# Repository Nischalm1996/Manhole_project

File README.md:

# Manhole_project

## Pin Connection from Board 
| Pin Name  | Digital Pin                            |
|-----------|----------------------------------------|
|SCK        | D13                                    |
| MOSI      | D11                                    |
| OK        | D6                                     |
| LEFT      | D10                                    |
| RIGHT     | D8                                     |
| RST       | D12                                    |
| RED       | D0                                     |
| GREEN     | A6                                     |
| BLUE      | A7                                     |
| MQ2       | A2                                     |
| MQ7       | A3                                     |
| MQ06      | A1                                     |
| MQ135     | A0                                     |

### MODULES USED
- DISPLAY 16x2 I2C
- SMOKE SENSOR (MQ02,MQ06,MQ07,MQ135)
- MQ02 (Methane, Butane, LPG, Hydrogen)
- MQ07 (CO, benzene)
- MQ06 (iso-butane, propane, LPG, LNG)
- MQ135 (NH3, NOx, alcohol,CO2)
- NAVIGATION BUTTON
- RGB LED
- GSM

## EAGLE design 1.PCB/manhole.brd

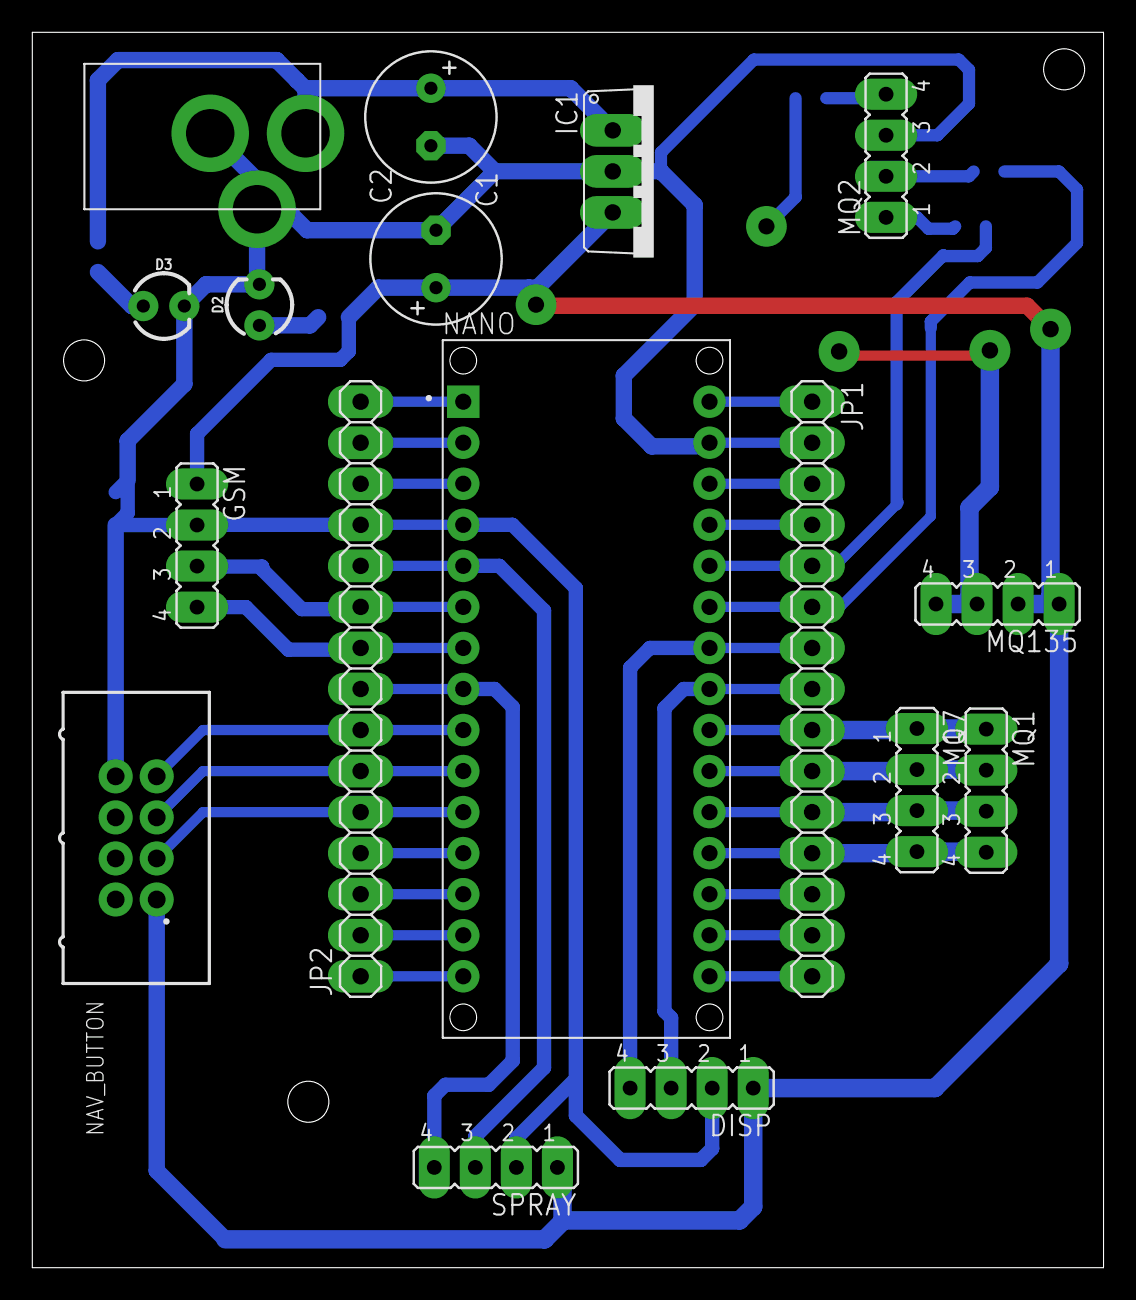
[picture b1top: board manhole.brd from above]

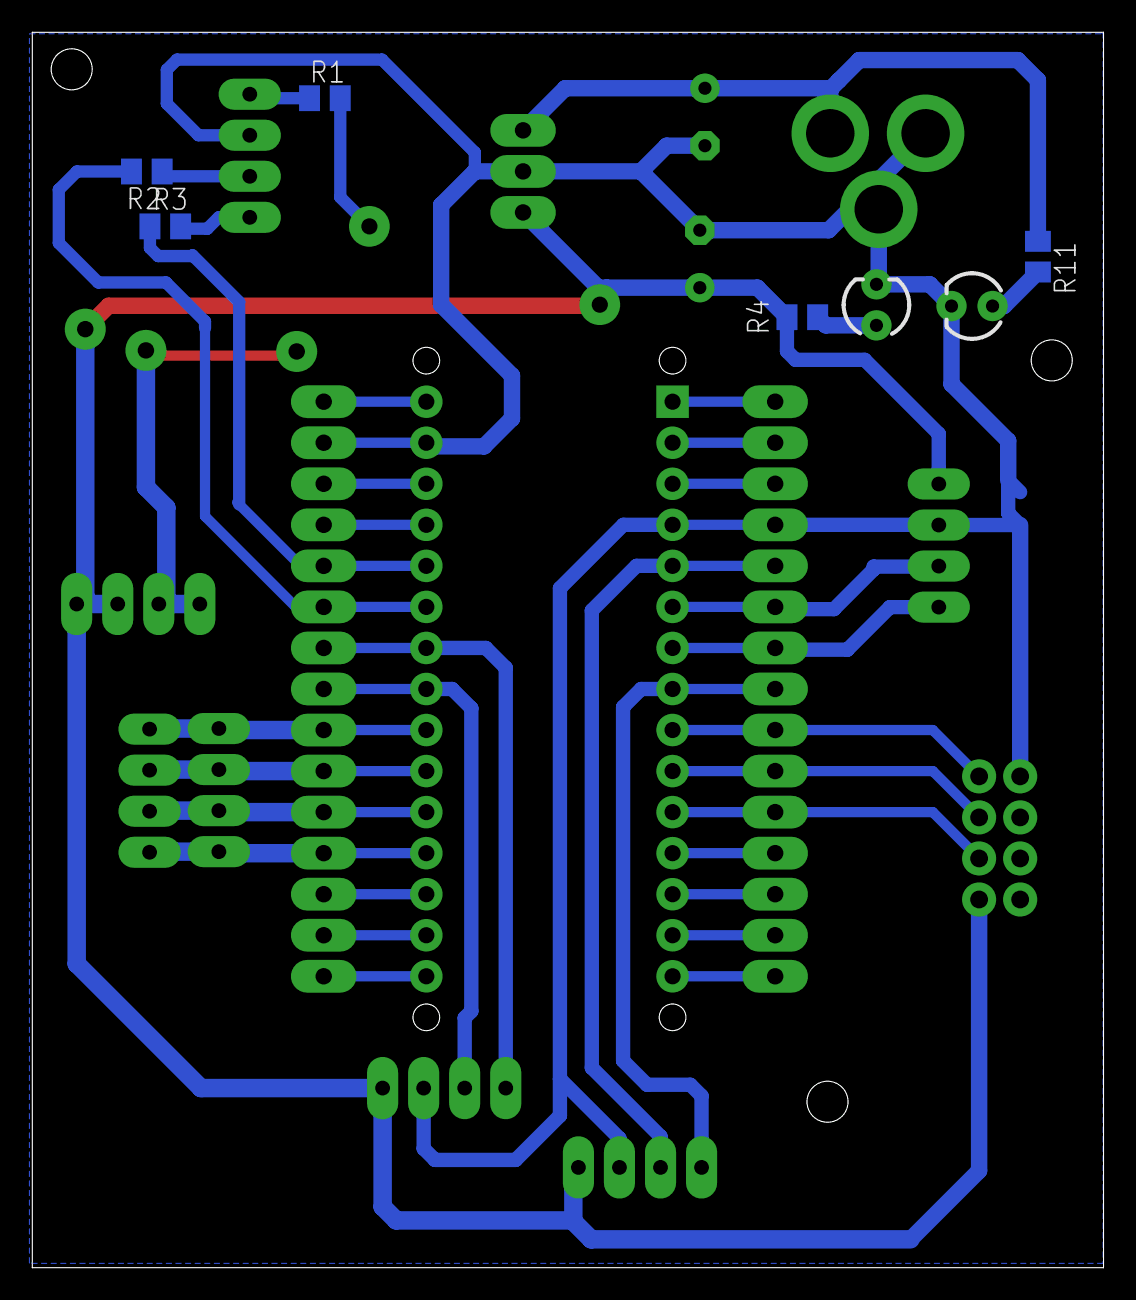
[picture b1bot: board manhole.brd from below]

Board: 2 copper layers, 66.3 x 76.5 mm, 22 parts (5 on the bottom side), 36 nets.

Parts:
C1, C2: E3,5-8
D2, D3: LED_3MM
DC_JACK: 2.1MMJACKTHM; PJ-102A
DISP: JP4
GSM: JP4
IC1: 7805TV; TO220V
JP1, JP2: 1X15
MQ1, MQ2, MQ7, MQ135: JP4
NANO: A000005; MODULE_A000005
NAV_BUTTON: 61200821621
R1, R2, R3: 300r; M0805
R4, R11: 1k; M0805
SPRAY: JP4

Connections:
3V3: JP1.14, NANO.17
5V: C2.+, DISP.1, GSM.1, IC1.3, MQ135.1, MQ135.2, NAV_BUTTON.1, R4.1, SPRAY.1
5V0: JP1.4, NANO.27
9_IN: C1.+, DC_JACK.TIP, IC1.1, R11.1
AREF: JP1.13, NANO.18
BLUE: MQ2.1, R3.1
BLUE1: JP1.5, NANO.26, R3.2
D0: JP2.15, NANO.1
D1: JP2.14, NANO.2
D9: JP2.4, NANO.12
GND: C1.-, C2.-, D2.K, D3.K, DC_JACK.RING, DC_JACK.RING_SW, DISP.2, GSM.2, IC1.2, JP1.2, JP2.12, MQ2.3, MQ135.3, MQ135.4, NANO.4, NANO.29, NAV_BUTTON.8, SPRAY.2
GREEN: MQ2.2, R2.1
GREEN1: JP1.6, NANO.25, R2.2
IN1: JP2.11, NANO.5, SPRAY.3
IN2: JP2.8, NANO.8, SPRAY.4
LEFT: JP2.6, NANO.10, NAV_BUTTON.5
MOSI: JP2.2, NANO.14
MQ2A0: JP1.9, MQ1.1, MQ7.1, NANO.22
MQ6A0: JP1.10, MQ1.2, MQ7.2, NANO.21
MQ7A0: JP1.11, MQ1.3, MQ7.3, NANO.20
MQ135A0: JP1.12, MQ1.4, MQ7.4, NANO.19
unnamed: D2.A, R4.2
unnamed: D3.A, R11.2
OK: JP2.7, NANO.9, NAV_BUTTON.7
RED: MQ2.4, R1.1
RED1: JP2.3, NANO.13, R1.2
RESET_1: JP2.13, NANO.3
RESET_2: JP1.3, NANO.28
RIGHT: JP2.5, NANO.11, NAV_BUTTON.3
RST: JP2.1, NANO.15
RX_GSM: GSM.3, JP2.10, NANO.6
SCK: JP1.15, NANO.16
SCL: DISP.4, JP1.7, NANO.24
SDA: DISP.3, JP1.8, NANO.23
TX_GSM: GSM.4, JP2.9, NANO.7
VIN: JP1.1, NANO.30

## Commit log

2021-03-16 added PCB
2021-03-16 PCB added
2021-04-16 added schematic
2021-04-16 updated structure
2021-04-17 SENSOR-MQ03,02,07,135 codes dumped
2021-04-17 added rgb led
2021-04-20 sensor pin updates
2021-04-21 MQ sensors gas detections
2021-04-23 title name change
2021-04-28 added display and gsm
2021-04-28 edited button menu and gsm
2021-04-28 mq06 updated
2021-04-28 made changes to menu
2021-04-29 added spraymotor
2021-04-29 made changes to code on menu
2021-04-29 prefinal commit
2021-05-03 update pre final need to add ppm
2021-05-03 Create workspace.code-workspace
2021-05-03 pins and gas detection details updated
2021-05-03 corrected as per your link
2021-05-03 removed mq03 sensor
2021-05-03 final commit
2021-05-04 updated PCB
2021-05-09 optimised for memory
2021-05-09 Revert "updated PCB"
    This reverts commit e032bd37680646525048ee8d74092bea044d5abf.
2021-05-09 final_commit v2

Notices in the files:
parts and their libraries:
SparkFun-LED: Licensing: Creative Commons ShareAlike 4.0 International - https://creativecommons.org/licenses/by-sa/4.0
Wurth_Connectors_WR-BHD: Copyright: Würth Elektronik
